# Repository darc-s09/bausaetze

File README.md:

Bausätze des OV S09
===================

Seit mehreren Jahren haben wir im Ortsverband verschiedene
Bastelaktivitäten laufen, vorranging finden diese bei Veranstaltungen
der "Technischen Sammlungen Dresden" statt, in deren Räumen sich
unsere Klubstation DL0TSD befindet.

Während der Bausatz des LED-Thermometers sein eigenes Repository hier
besitzt, hatten wir die Software und auch Dokumentation für andere
Bausätze historisch auf einem privaten Openproject-Server gehostet.
Von dort wurden sie hier nach Github migriert.

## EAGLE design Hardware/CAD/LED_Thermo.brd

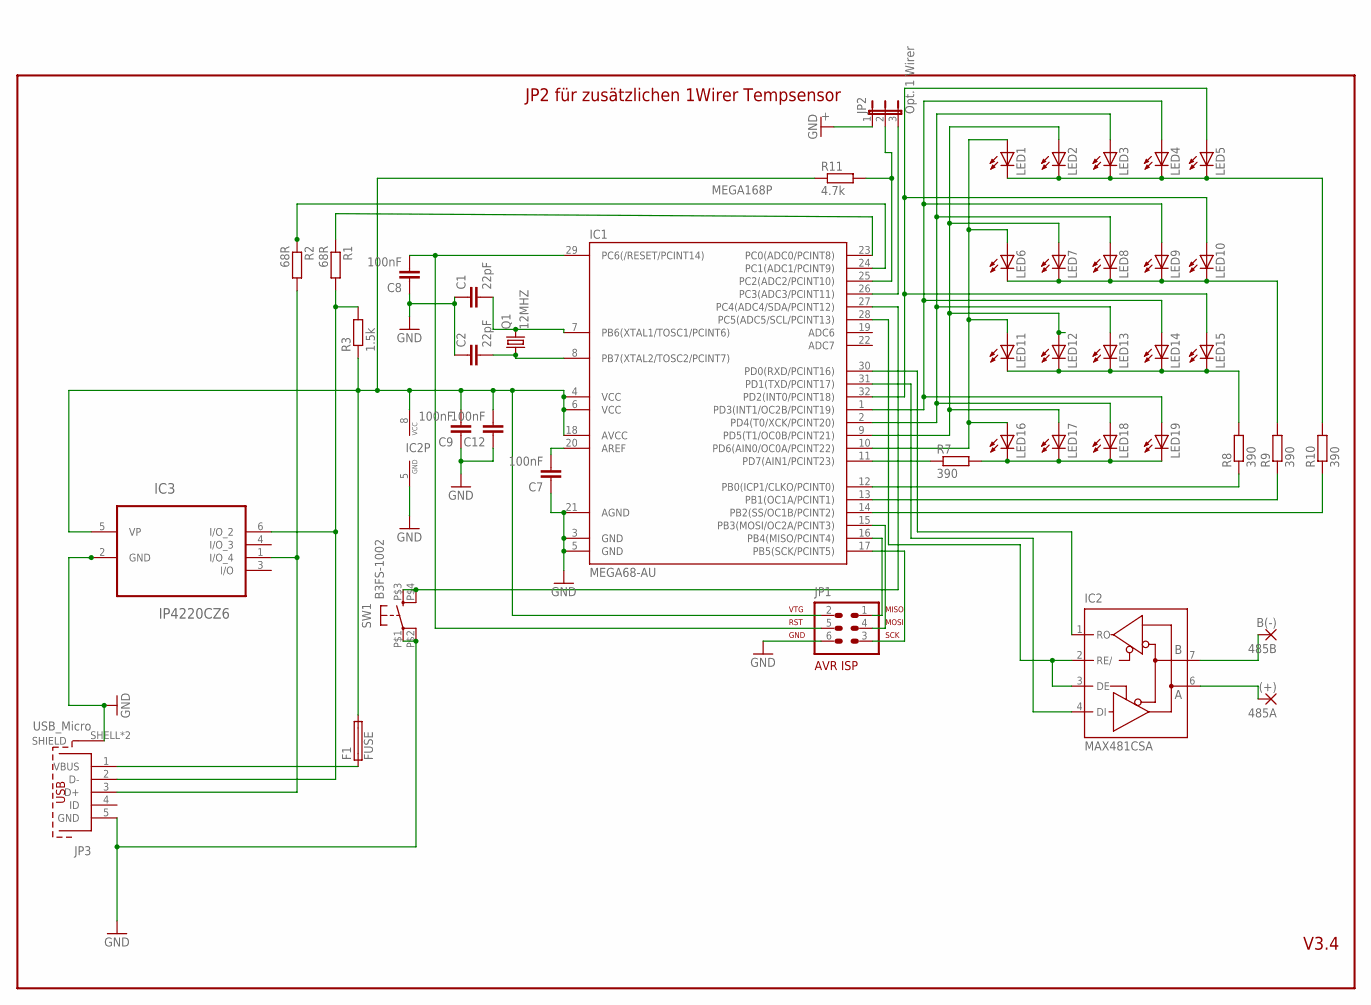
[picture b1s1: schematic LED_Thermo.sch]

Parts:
485A: (+); 2,54/1,0
485B: B(-); 2,54/1,0
C1, C2: 22pF; C0805
C7, C8, C9, C12: 100nF; C0805
F1: FUSE; FUSE_1206
IC1: MEGA68-AU; TQFP32-08
IC2: MAX481CSA; SO08
IC3: IP4220CZ6; SOT95P275X110-6N
JP1: AVR-ISP-6
JP2: Opt. 1 Wirer; JP2
JP3: USB_Micro; 614105150721
LED1, LED2, LED3, LED4, LED5, LED6, LED7, LED8, LED9, LED10, LED11, LED12, LED13, LED14, LED15, LED16, LED17, LED18, LED19: LED3MM
Q1: 12MHZ; HC18U-V
R1, R2: 68R; M0805
R3: 1.5k; M0805
R7, R8, R9, R10: 390; M0805
R11: 4.7k; M0805
SW1: B3FS-1002

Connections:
GND: C1.1, C2.1, C7.1, C8.1, C9.1, C12.1, IC1.3 (GND), IC1.5 (GND), IC1.21 (AGND), IC2.5 (GND), IC3.2 (GND), JP1.6, JP2.1, JP3.5 (GND), JP3.SHELL (SHIELD), JP3.SHELL1 (SHIELD), SW1.P$1, SW1.P$2 (P1)
unnamed: IC1.23 (PC0(ADC0/PCINT8)), R1.1
unnamed: IC1.10 (PD6(AIN0/OC0A/PCINT22)), LED1.A, LED6.A, LED11.A, LED16.A
unnamed: IC1.24 (PC1(ADC1/PCINT9)), R2.1
unnamed: F1.1, JP3.1 (VBUS)
unnamed: IC1.9 (PD5(T1/OC0B/PCINT21)), LED2.A, LED7.A, LED12.A, LED17.A
unnamed: IC1.27 (PC4(ADC4/SDA/PCINT12)), SW1.P$3 (S), SW1.P$4 (S1)
unnamed: IC3.1 (I/O_4), JP3.3 (D+), R2.2
unnamed: IC3.6 (I/O_2), JP3.2 (D-), R1.2, R3.2
unnamed: IC1.2 (PD4(T0/XCK/PCINT20)), LED3.A, LED8.A, LED13.A, LED18.A
unnamed: LED16.K (C), LED17.K (C), LED18.K (C), LED19.K (C), R7.2
unnamed: LED11.K (C), LED12.K (C), LED13.K (C), LED14.K (C), LED15.K (C), R8.2
unnamed: IC1.1 (PD3(INT1/OC2B/PCINT19)), LED4.A, LED9.A, LED14.A, LED19.A
unnamed: LED6.K (C), LED7.K (C), LED8.K (C), LED9.K (C), LED10.K (C), R9.2
unnamed: LED1.K (C), LED2.K (C), LED3.K (C), LED4.K (C), LED5.K (C), R10.2
unnamed: IC1.17 (PB5(SCK/PCINT5)), JP1.3
unnamed: IC1.16 (PB4(MISO/PCINT4)), JP1.1
unnamed: IC1.15 (PB3(MOSI/OC2A/PCINT3)), JP1.4
unnamed: IC1.12 (PB0(ICP1/CLKO/PCINT0)), R8.1
unnamed: IC1.13 (PB1(OC1A/PCINT1)), R9.1
unnamed: C7.2, IC1.20 (AREF)
unnamed: C8.2, IC1.29 (PC6(/RESET/PCINT14)), JP1.5
unnamed: IC1.14 (PB2(SS/OC1B/PCINT2)), R10.1
unnamed: IC1.32 (PD2(INT0/PCINT18)), LED5.A, LED10.A, LED15.A
unnamed: C1.2, IC1.7 (PB6(XTAL1/TOSC1/PCINT6)), Q1.2
unnamed: C2.2, IC1.8 (PB7(XTAL2/TOSC2/PCINT7)), Q1.1
unnamed: 485B.1, IC2.7 (B)
unnamed: IC1.31 (PD1(TXD/PCINT17)), IC2.4 (DI)
unnamed: IC1.30 (PD0(RXD/PCINT16)), IC2.1 (RO)
unnamed: IC1.28 (PC5(ADC5/SCL/PCINT13)), IC2.2 (RE/), IC2.3 (DE)
unnamed: 485A.1, IC2.6 (A)
unnamed: IC1.26 (PC3(ADC3/PCINT11)), JP2.3
unnamed: IC1.11 (PD7(AIN1/PCINT23)), R7.1
unnamed: IC1.25 (PC2(ADC2/PCINT10)), JP2.2, R11.2
VCC: C9.2, C12.2, F1.2, IC1.4 (VCC), IC1.6 (VCC), IC1.18 (AVCC), IC2.8 (VCC), IC3.5 (VP), JP1.2, R3.1, R11.1

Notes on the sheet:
MEGA168P
V3.4
JP2 für zusätzlichen 1Wirer Tempsensor

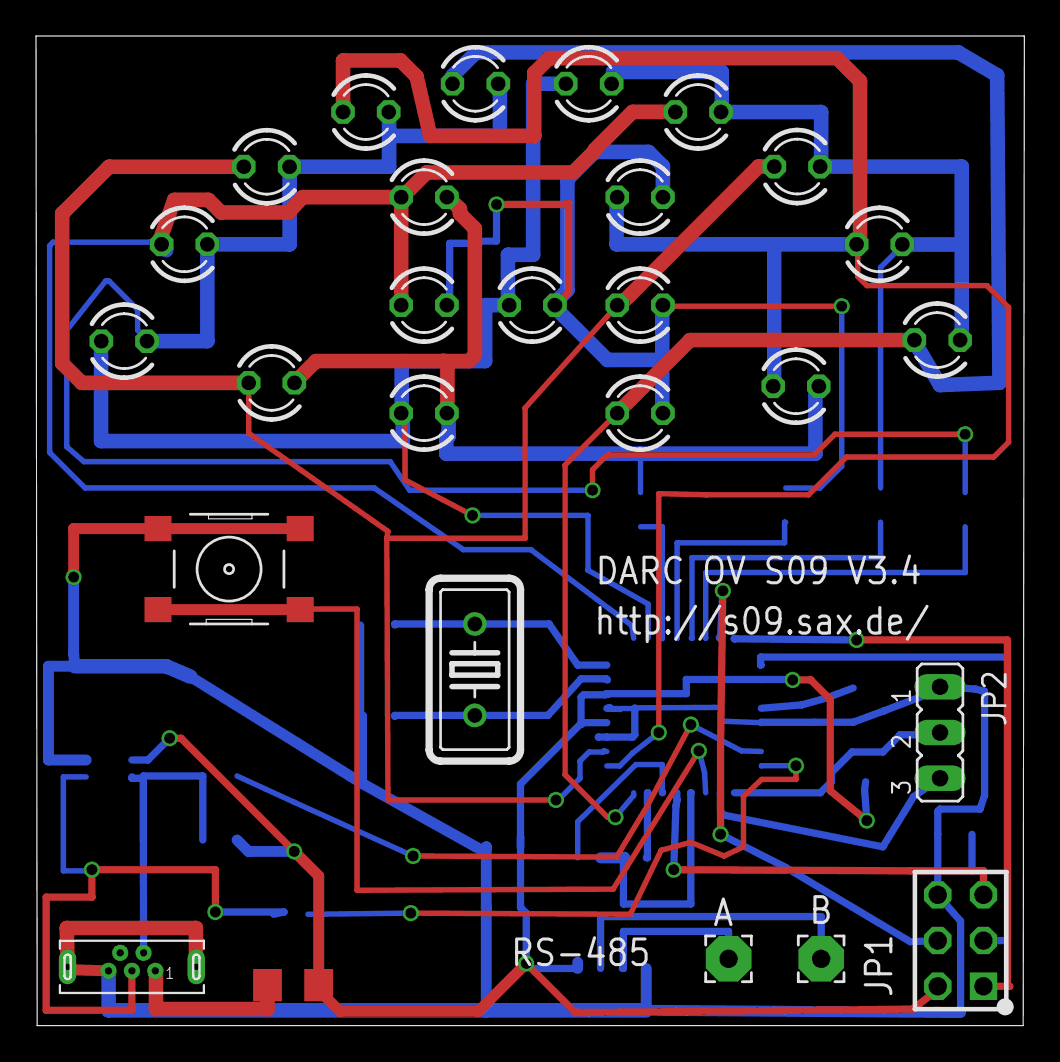
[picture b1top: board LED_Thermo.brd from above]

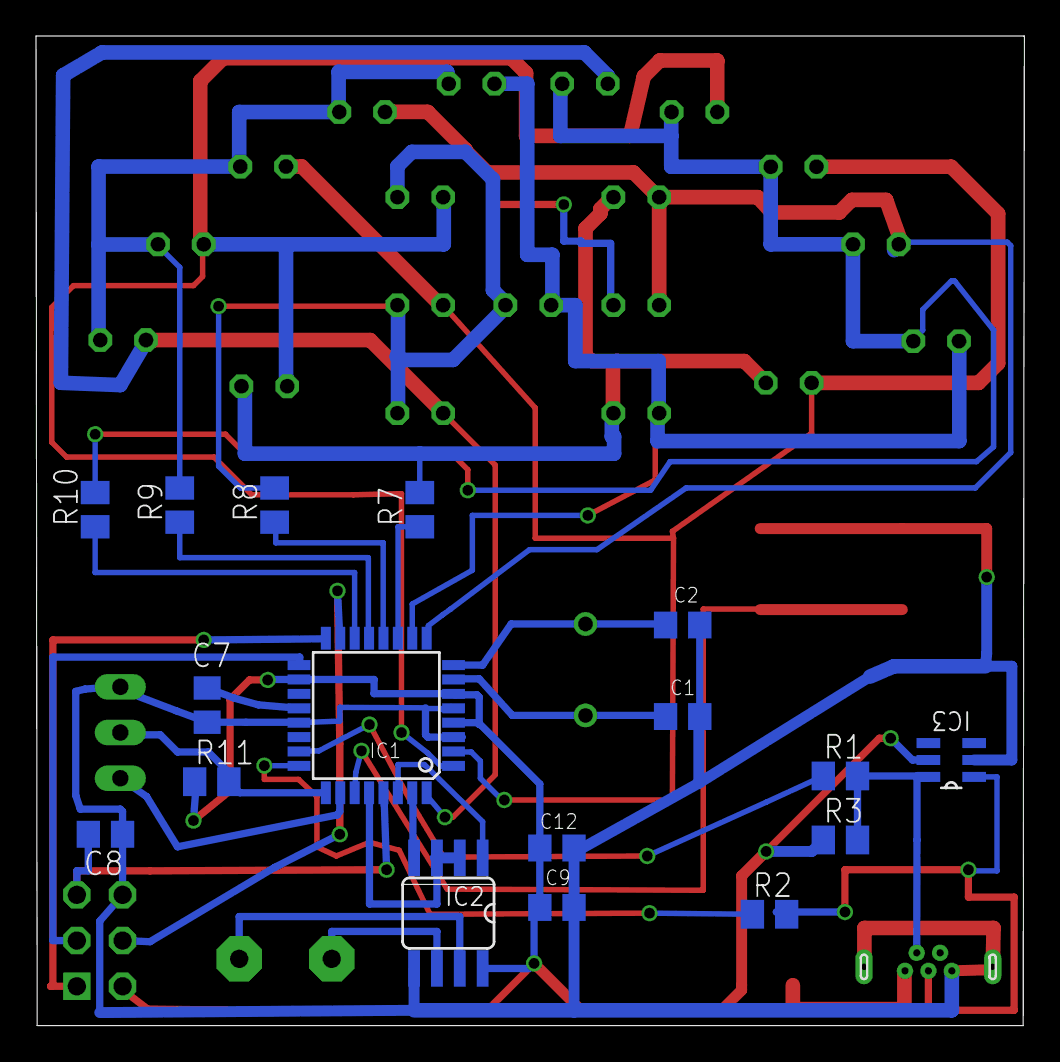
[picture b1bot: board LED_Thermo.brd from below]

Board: 2 copper layers, 54.8 x 54.9 mm, 44 parts (17 on the bottom side), 35 nets.

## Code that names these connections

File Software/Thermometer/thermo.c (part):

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    // Mittelstellung sein, damit das funktioniert. Befindet es sich
    // zu weit Richtung GND, wird der Bootloader aktiviert.  Befindet
    // es sich nahe am Vcc-seitigen Anschlag, ist es nicht von einem
    // unbeschalteten JP2 (Pullup nach PC3) unterscheidbar.
    uint8_t adc2 = ADC_read_ADC2();
    if (adc2 < 240)
    {
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{
/* Belegung PORTB

PB0 = Kathode LED 11,12,13,14,15
PB1 = Kathode LED  6, 7, 8, 9,10
PB2 = Kathode LED  1, 2, 3, 4, 5
PB3 = MOSI / Jumper Konfig
PB4 = MISO / Jumper Konfig
PB5 = SCK  / Jumper Konfig
PB6 = Quarz
PB7 = Quarz
Bei Init werden die PORTS PB0 bis PB2 als Ausgang gesetzt
und die PORTS PB3 bis PB7 als Ausgang
PULLUP Widerstaende zur Abfrage der Jumper Stellung werden im Programm gesetzt.

*/
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    PORTB =0b00000000;

/* Belegung PORTC
PC0 = USB D-
PC1 = USB D+
PC2 = 1 Wirer DATA 4,7K Widerstand geht auf Masse, in der Rev. 3.3 falsch?
PC3 = 1 Wirer Power
PC4 = Taster Start Wuerfel, Eingang mit internen Pull_UP
PC5 = RX/TX Umschaltung fuer RS485 HI=TX LOW=RX
PC6 = RESET
PC7 = NC
Alle Ports auf Eingang, bis auf PORT PC5 AUSGANG fuer DEBUG Ausgabe
PULLUP Widerstand vom PORT PC2,PC4 aktive
*/
    DDRC =  0b00100000;
    PORTC = 0b00010000;
/* Belegung PORTD
PD0 = RXD (485)
PD1 = TXD (485)
PD2 = Anode LED  5,10,15    > Spalte
PD3 = Anode LED  4,9,14,19  > Spalte
PD4 = Anode LED  3,8,13,18  > Spalte
PD5 = Anode LED  2,7,12,17  > Spalte
PD6 = Anode LED  1,6,11,16  > Spalte
PD7 = Kathode LED 16,17,18,19 > Zeile
Port PD2 bis PD7 auf Ausgang



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
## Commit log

2019-10-16 Create top-level structure.
2019-10-17 Create some more structure
2019-10-19 Versionstsand Januar 2019 eingestellt
2019-10-19 PDF Dateien der Schaltplaene angehangen
2019-10-21 Tabs durch Leerzeichen ersetzt, Leerzeichen am Ende der Zeile entfernt.
    Umlaute ersetzt, damit man es auch in Umgebungen lesen kann, die kein
    Latin-1 mehr benutzen.
2019-10-22 Schaltplaene ueberarbeite, Board noch nicht komplett geroutet
2019-10-24 Schaltplaene und Board in Eagel Version 7 ueberfuehrt. Gerberdateien vom aktuellen Entwicklungsstand erzeugt
2019-10-25 Sicherung eingefuegt, Gerberdateien aktualisiert
2019-10-26 Taster eingefuegt, Gerberdateien ueberarbeitet
2019-10-27 USB-Schutzschaltung,12MHZ Quarz integriert,Layout + Loetstopmake optimiert
2019-10-27 Bestückungsdruck vergrößert
2019-10-27 Noch ein wenig an der Schrift herum gefeilt
2019-10-27 Offenbar lassen sich vernünftige Strichstärken der Schrift nur mit Vektorfonts erreichen.
2019-10-28 Batchdatei fuer CAM Job und Konfiguration fuer DRC ins Projekt integriert
2019-10-28 Gerberdaten neu erzeugt nach den diversen Änderungen
    Dies ist die Produktionsfassung, die dem Fertiger in Auftrag gegeben
    wurde.
2019-11-01 c und h Files ueberarbeitet, dabei Fehler in Schaltplan gefunden, diesen beseitigt aber keine neuen Gerberdateien erzeugt
2019-11-02 Kommentare im Programm ueberarbeitet
2019-11-04 Wuerfel funktioniert, geht aber nur ueber UART anzusteuern. Taster folgt ...
2019-11-04 Einfacher Quarzfrequenz-Test: f_CPU/2 an PB3 (pin 4 ISP)
2019-11-05 Wuerfel Spezial Mode eingearbeitet
2019-11-05 Zweiten Zufallsgenerator eingebaut und Fehler Bereinigung
2019-11-06 Drop Windows .exe extensions
2019-11-06 Remove dependency directory from SVN
2019-11-07 Vorbereitung des Multiplayer Modes
2019-11-07 Add .hg to svn:ignore
2019-11-07 Add virgin bootloadHID 2012-12-08
    https://www.obdev.at/products/vusb/bootloadhid.html
2019-11-07 Update for our project
2019-11-07 Change default AVRDUDE programmer
2019-11-07 This binary is for FreeBSD.
2019-11-07 This is the Linux commandline tool
2019-11-07 Move the binaries into their own subdir
2019-11-07 Remove useless "executable" properties
2019-11-07 Move binaries into their own subdir.
2019-11-08 Switch zum Wuerfeln aktiviert, PORTC PIN 4
2019-11-11 First version of Nachtlicht
2019-11-12 Verbesserung des Multiplayer Modes
2019-11-12 Rename formal argument in ticks_to_ms()
    Using "ticks" both as formal argument as well as global
    variable was confusing.
2019-11-12 Move LED updates into the main loop, only set flag in ISR
2019-11-12 Avoid "stuck dim LED" effect
    During measurement, do not enable PWM output already. Otherwise, with
    OCR0A = 0, it resulted in a one-clock-cycle (7 µs) turn-on period of
    the LED already, causing it to be dim.
    Abort current measurement if measurement time exceeds the period
    defined for full darkness; this avoids the measurement taking
    virtually forever, so the next measurement was already triggered 10
2019-11-12 "seconds" can be made private to WDT_vect.
2019-11-12 Implement J2 1-2: dim LED jumper
2019-11-13 Vorbereitung der Funktionsauswahl ueber Jumper
2019-11-13 Add local variables, for Emacs.
2019-11-13 Move variable definitions into source file.
2019-11-13 Avoid "value computed is not used" warning
2019-11-14 Kleine Aenderung Abfrage Wuerfel Modus
2019-11-15 Implementierung der verschiedenen Wuerfel Modis abgeschlossen
2019-11-16 Move the "all" target to be the first one.
    Only that way it can work as intended.
2019-11-16 Move more variable declarations from header to source file.
2019-11-17 Ersatz von "magic numbers" durch symbolische Konstanten
2019-11-17 Entfernen der unbenutzten Funktion warte_sekunde()
2019-11-18 UART kann jetzt per UART_DEBOG 0 rausgenommen werden
2019-11-18 Auslagern aller UART-spezifischer Dinge nach uart.c.
    Auf diese Weise bleiben in thermo.c nur noch wenige #ifdefs, und
    es wird alles übersichtlicher.
2019-11-20 F_CPU auf 12 MHz
2019-11-20 12MHZ Teiler 1
2019-11-20 Don't use the timer 0 prescaler even for 12 MHz
2019-11-20 Add 1wire stuff
2019-11-20 1wire-Dateien einbinden (beispielhaft)
2019-11-20 umgestellt auf 12MHZ, counter fuer Tasterabfrage rausgenommen, Rest folgt am Donnerstag
2019-11-21 Plakat
2019-11-21 Preiskorrektur nach genauer Kalkulation
2019-11-21 counter rausgeschmissen, interne Temperaturmessung auf Interrupt umgestellt
2019-11-21 Move ow_power() into its own function
2019-11-21 Re-add Emacs local variables that vanished in r59.
    Move beer-ware license into its own paragraph.
2019-11-21 Vereinheitlichung des Einrückungs-Stils
    Keinerlei inhaltliche Änderungen.
2019-11-22 Vereinfachung des ADC-Auslesens (ADLAR benutzen)
2019-11-22 Remove unneeded files from SVN
2019-11-22 Oops, makedep.mk is still needed ...
2019-11-22 Erster Versuch für DS18B20-Einbindung als Temperatursensor
2019-11-22 Temperaturmessung doch 10bittig.
2019-11-22 Interner Temperatursensor jetzt auch über Rechnung in degC
    Damit sind der interne Sensor und der DS18B20 in der Behandlung
    gleichwertig. Nun muss nur noch die LED-Bandanzeige angepasst
    werden.
2019-11-22 Jumperabfrage begonnen, funktioniert aber nicht
2019-11-22 Do not use 1wire by now
2019-11-22 Umbau LED-Band auf generischen Bereich
2019-11-22 Untabify
2019-11-22 Fertigstellen Jumper-Erkennung
2019-11-22 Korrektur Klammersetzung bei Temperaturberechnung
    Korrektur off-by-one error LED Bandanzeige oberer Wert
2019-11-22 LED Helligkeit erhöhen
2019-11-23 Nachtlicht CAD-Daten
2019-11-23 Jumpersetting implementiert
2019-11-23 Implement flicker mode ("Kerze")
2019-11-23 "Random" tables from Fabian
2019-11-23 Random update from Fabian
2019-11-23 Power up the 1wire bus before probing
2019-11-23 Keep 1wire bus powered all the time
2019-11-23 Return actual probe result
2019-11-30 remove unneeded delay
2019-11-30 Fix order in set_dq()
2019-11-30 Preserve interrupt status in internal functions.
    Keep interrupts disabled when turning on strong pullup
2019-12-01 Bausatzbeschreibung Wuerfel begonnen
2019-12-01 Alternatives Thermometer mit 1wire-Sensor.
    Nur für den Test erstmal, um das 1wire-Setup zu debuggen. Der Code war
    ursprünglich für eine völlig andere Hardware konzipiert und wurde nur
    schnell adaptiert.
2019-12-01 Make OW_POWER_PIN an output, actually
2019-12-02 Fix value of R1 to match the one actually used.
    Add PDF of schematics, and archive of entire Kicad project.
2019-12-02 Schaltplan und Kicad-Projekt für Webseite.
2019-12-02 CAM data for Nachtlicht, as ordered at PCB factory
2019-12-02 Implement Get_ROMCode
    Currently only used when UART debugging is enabled.
2019-12-02 Implement device detection for 1wire sensors
2019-12-02 Add Configure_DS18B20()
    Configures a connected DS18B20 for 9-bit operation, so the conversion
    time can be reduced to 100 ms.
2019-12-04 Allow UART_DEBUG override from commandline
2019-12-04 Move ADC_init() into its own function
2019-12-05 Select PC3 for powering the external pull-up while probing
2019-12-05 Implement basic software calibration of internal sensor
2019-12-10 Gesonderte Build-Konfiguration mit UART Debugging.
2019-12-11 Umorganisation der Temp-Sensor-Kalibrierung
    ADC_Init() übernimmt Parameter, mit dem festgelegt wird, ob
    der ADC für eine Temperaturmessung oder für die Poti-Abfrage
    initialisiert werden soll. Im Kalibriermodus wechseln sich
    beide Betriebsarten ab.
    Die Messung erfolgt wieder durch Timer 1 gesteuert, allerdings
    schneller als im Normalbetrieb.
2019-12-11 Einstellung von Timer 1 komplett innerhalb Timer_Init()
2019-12-12 Abspeichern und Einlesen des Kalibrierwertes interner Sensor im EEPROM
2019-12-13 Do not disable power of 1wire Subsystem again
    Powering off the 1wire bus in ADC_read_ADC2() caused any potentially
    connected 1wire sensor to not be detected anymore.
    Just keep the 1wire subsystem enabled all the time.
2020-02-12 Angefangen mit der Bausatzbeschreibung Wuerfel
2024-07-18 Add a simple README
2026-03-26 Copy over sources from µracoli repo
    Use slightly different Makefile here.
2026-03-31 First attempt of adapting to re-wired boards
    Effectively, swap PB0..2 and PD5..7
    PB0..2 now used as capacitive touchpads,
    PD5..7 now used as LED column selection.
2026-04-03 Update µracoli to latest source
    This fixes a compile-time warning about an undefined macro.
2026-06-21 Fix DDRx handling
    DDRD must be initialized during startup, to enable LED outputs.
    Reading back DDRB in display_leds() is not needed.

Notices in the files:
parts and their libraries:
InputOutputIO: Copyright: Würth Elektronik
